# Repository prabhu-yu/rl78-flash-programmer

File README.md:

# RL78-flash-programmer
Visit the [RL78 Flash Prog. Webpage](https://prabhu-yu.github.io/projects/rl78/rl78-flash-prog/) for details.

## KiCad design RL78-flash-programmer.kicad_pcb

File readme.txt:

This is a PCB board for Renesas RL78 Flash programmer. It is designed using KiCAD.
This board needs to be used along with Renesas Flash Programmer GUI.
This PCB desgin implements "Sample Type B circuit (1-Wire UART)" as explained in the below customer notification given by Renesas itslef.
Renesas Programmer customer Notification is openly available on internet. - https://www.renesas.com/us/en/document/man/renesas-flash-programmer-sample-circuit-programming-using-pcs-serial-port

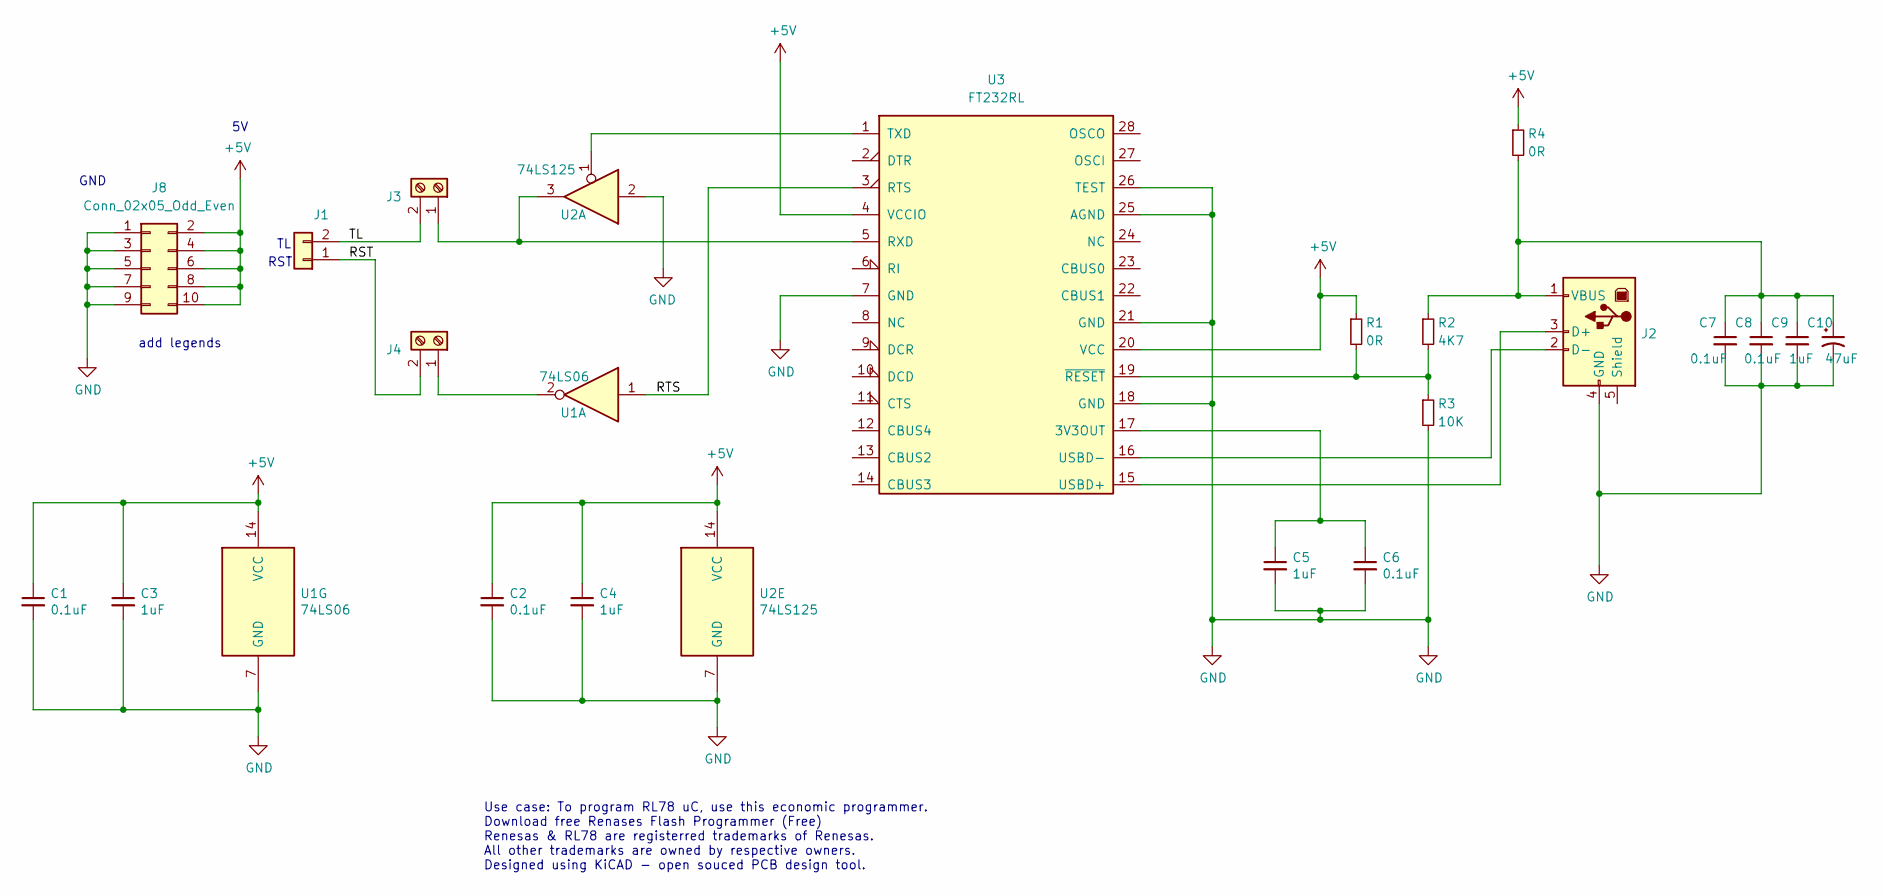
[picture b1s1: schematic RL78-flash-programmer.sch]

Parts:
C1, C2, C6, C7, C8: 0.1uF; C_1206_3216Metric_Pad1.42x1.75mm_HandSolder
C3, C4, C5, C9: 1uF; C_1206_3216Metric_Pad1.42x1.75mm_HandSolder
C10: 47uF; CP_Radial_D8.0mm_P2.50mm
J1: Conn_01x02; PinHeader_1x02_P2.54mm_Vertical
J2: USB_B; USB_B_OST_USB-B1HSxx_Horizontal
J3, J4: Screw_Terminal_01x02; TerminalBlock_Phoenix_MKDS-1,5-2_1x02_P5.00mm_Horizontal
J8: Conn_02x05_Odd_Even; PinHeader_2x05_P2.54mm_Vertical
R1, R4: 0R; R_1206_3216Metric_Pad1.42x1.75mm_HandSolder
R2: 4K7; R_1206_3216Metric_Pad1.42x1.75mm_HandSolder
R3: 10K; R_1206_3216Metric_Pad1.42x1.75mm_HandSolder
U1: 74LS06; DIP-14_W7.62mm
U2: 74LS125; DIP-14_W7.62mm
U3: FT232RL; SSOP-28_5.3x10.2mm_P0.65mm

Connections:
+5V: C1.1, C2.1, C3.1, C4.1, J8.2, J8.4, J8.6, J8.8, J8.10, R1.1, R4.1, U1.14 (VCC), U2.14 (VCC), U3.4 (VCCIO), U3.20 (VCC)
/RST: J1.1, J4.2
/RTS: U1.1, U3.3 (RTS)
/TL: J1.2, J3.2
GND: C1.2, C2.2, C3.2, C4.2, C5.2, C6.2, C7.2, C8.2, C9.2, C10.2, J2.4 (GND), J8.1, J8.3, J8.5, J8.7, J8.9, R3.2, U1.7 (GND), U2.2, U2.7 (GND), U3.7 (GND), U3.18 (GND), U3.21 (GND), U3.25 (AGND), U3.26 (TEST)
unnamed: C5.1, C6.1, U3.17 (3V3OUT)
unnamed: C7.1, C8.1, C9.1, C10.1, J2.1 (VBUS), R2.1, R4.2
unnamed: J2.2 (D-), U3.16 (USBD-)
unnamed: J2.3 (D+), U3.15 (USBD+)
unnamed: J3.1, U2.3, U3.5 (RXD)
unnamed: J4.1, U1.2
unnamed: R1.2, R2.2, R3.1, U3.19 (~RESET~)
unnamed: U2.1, U3.1 (TXD)

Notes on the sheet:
RST
GND
add legends
Use case: To program RL78 uC, use this economic programmer. Download free Renases Flash Programmer (Free) Renesas & RL78 are registerred trademarks of Renesas. All other trademarks are owned by respective owners. Designed using KiCAD - open souced PCB design tool.

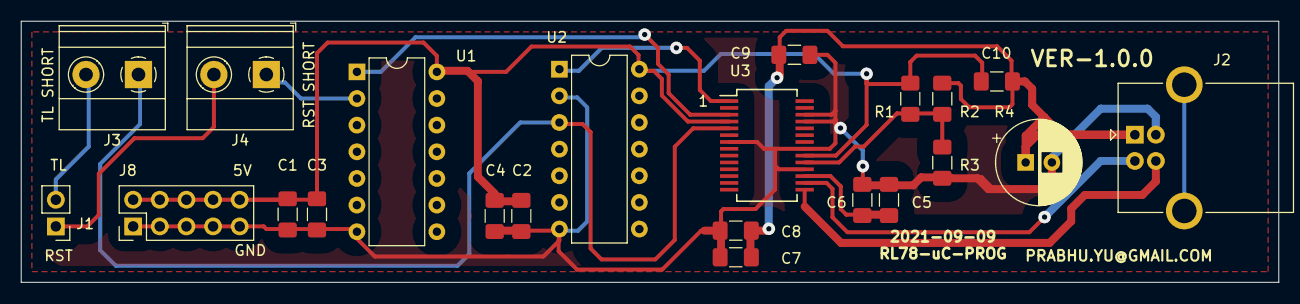
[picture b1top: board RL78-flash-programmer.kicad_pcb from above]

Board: 2 copper layers, 119.9 x 24.9 mm, 22 parts (0 on the bottom side), 13 nets.

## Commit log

2021-09-10 init
